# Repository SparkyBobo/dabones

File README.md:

# DaBones

DaBones is a Halloween animatronic rock show project combining mechanical characters, embedded electronics, lighting control, audio playback, and stage effects.

The goal is to create a repeatable live Halloween performance experience where animated characters perform as a band with synchronized movement, lighting, and effects.

## Project Status

Current release:

**DaBones v1.0 — Halloween 2026**

The focus of v1.0 is a complete, reliable show experience.

The goal is not to complete every possible feature. Future enhancements are intentionally deferred into later releases.

## System Overview

DaBones consists of several integrated systems:

* Animated characters
* Mechanical motion systems
* Embedded controllers
* Lighting and DMX control
* Audio and MIDI synchronization
* Stage infrastructure
* Special effects

## Engineering Approach

The project follows a release-based engineering model:

* Define the release before building
* Capture design decisions and tradeoffs
* Separate ideas from commitments
* Document why decisions are made
* Build platforms that support future expansion

## Repository Contents

```
docs/
    Release definitions
    Architecture documentation
    Inventory
    Decisions
    Field notes

hardware/
    Electronics designs
    Mechanical designs
    Related hardware files

firmware/
    Embedded software
```

## Relationship to Portfolio

DaBones is one project within a larger personal engineering portfolio.

The portfolio repository contains cross-project planning, engineering practices, and field notes.

## Current Goal

Deliver a complete Halloween 2026 show with a defined minimum viable feature set and a reliable operating experience.

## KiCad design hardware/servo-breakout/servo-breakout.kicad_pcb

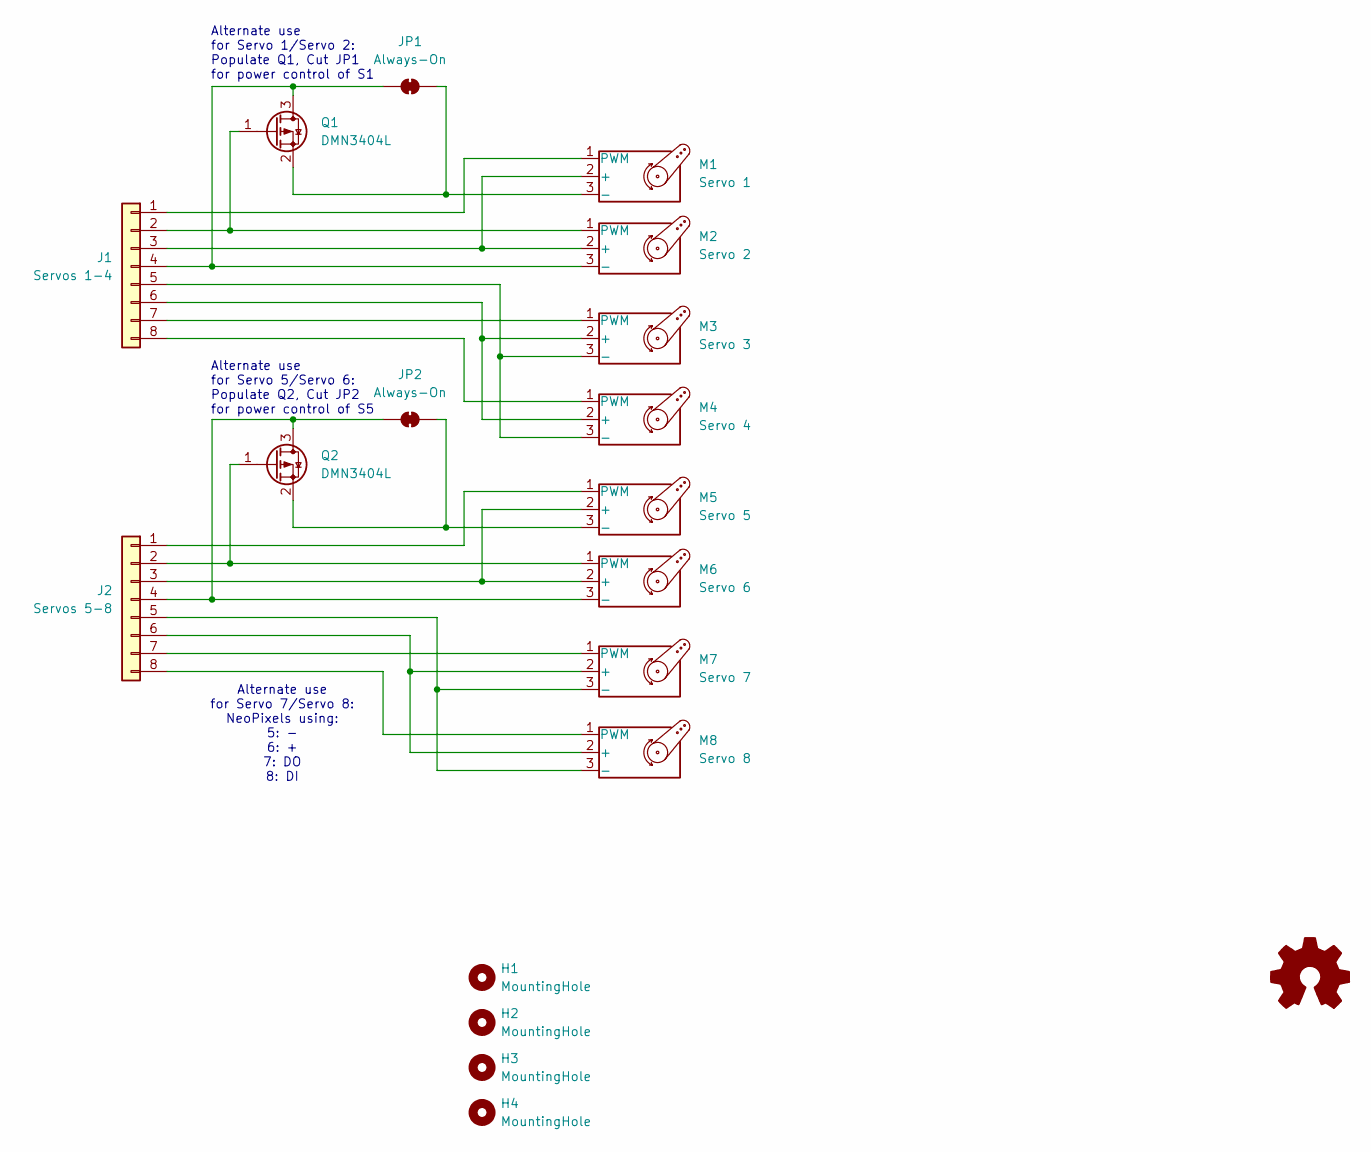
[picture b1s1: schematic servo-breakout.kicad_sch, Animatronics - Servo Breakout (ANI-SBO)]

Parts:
H1, H2, H3, H4: MountingHole; MountingHole_3.2mm_M3
J1: Servos 1-4; PhoenixContact_MCV_1,5_8-G-3.81_1x08_P3.81mm_Vertical
J2: Servos 5-8; PhoenixContact_MCV_1,5_8-G-3.81_1x08_P3.81mm_Vertical
JP1, JP2: Always-On; SolderJumper-2_P1.3mm_Bridged2Bar_RoundedPad1.0x1.5mm
M1: Servo 1; PinHeader_1x03_P2.54mm_Horizontal
M2: Servo 2; PinHeader_1x03_P2.54mm_Horizontal
M3: Servo 3; PinHeader_1x03_P2.54mm_Horizontal
M4: Servo 4; PinHeader_1x03_P2.54mm_Horizontal
M5: Servo 5; PinHeader_1x03_P2.54mm_Horizontal
M6: Servo 6; PinHeader_1x03_P2.54mm_Horizontal
M7: Servo 7; PinHeader_1x03_P2.54mm_Horizontal
M8: Servo 8; PinHeader_1x03_P2.54mm_Horizontal
Q1, Q2: DMN3404L; TSOT-23_HandSoldering

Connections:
unnamed: J1.1, M1.1 (PWM)
unnamed: J1.2, M2.1 (PWM), Q1.1 (G)
unnamed: J1.3, M1.2 (+), M2.2 (+)
unnamed: J1.4, JP1.2 (B), M2.3 (-), Q1.3 (D)
unnamed: J1.5, M3.3 (-), M4.3 (-)
unnamed: J1.6, M3.2 (+), M4.2 (+)
unnamed: J1.7, M3.1 (PWM)
unnamed: J1.8, M4.1 (PWM)
unnamed: J2.1, M5.1 (PWM)
unnamed: J2.2, M6.1 (PWM), Q2.1 (G)
unnamed: J2.3, M5.2 (+), M6.2 (+)
unnamed: J2.4, JP2.2 (B), M6.3 (-), Q2.3 (D)
unnamed: J2.5, M7.3 (-), M8.3 (-)
unnamed: J2.6, M7.2 (+), M8.2 (+)
unnamed: J2.7, M7.1 (PWM)
unnamed: J2.8, M8.1 (PWM)
unnamed: JP1.1 (A), M1.3 (-), Q1.2 (S)
unnamed: JP2.1 (A), M5.3 (-), Q2.2 (S)

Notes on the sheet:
Alternate use for Servo 7/Servo 8: NeoPixels using: 5: - 6: + 7: DO 8: DI
Alternate use for Servo 1/Servo 2: Populate Q1, Cut JP1 for power control of S1
Alternate use for Servo 5/Servo 6: Populate Q2, Cut JP2 for power control of S5

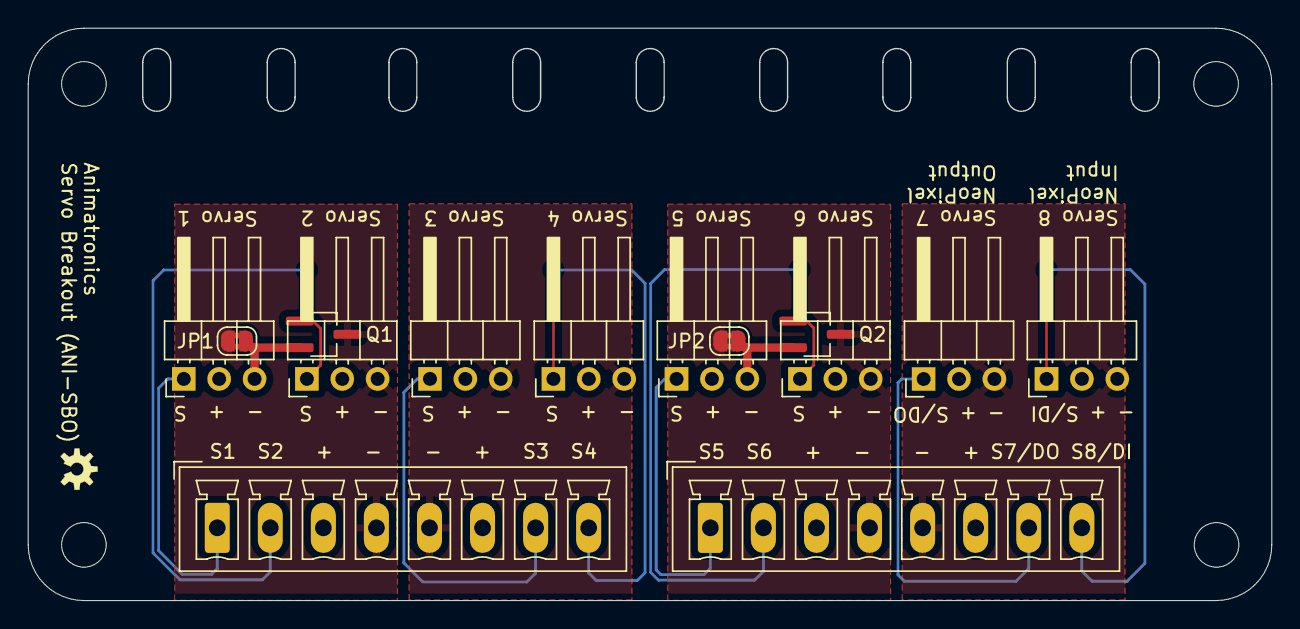
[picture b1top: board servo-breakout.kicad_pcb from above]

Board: 2 copper layers, 89.2 x 41.1 mm, 18 parts (0 on the bottom side), 18 nets.

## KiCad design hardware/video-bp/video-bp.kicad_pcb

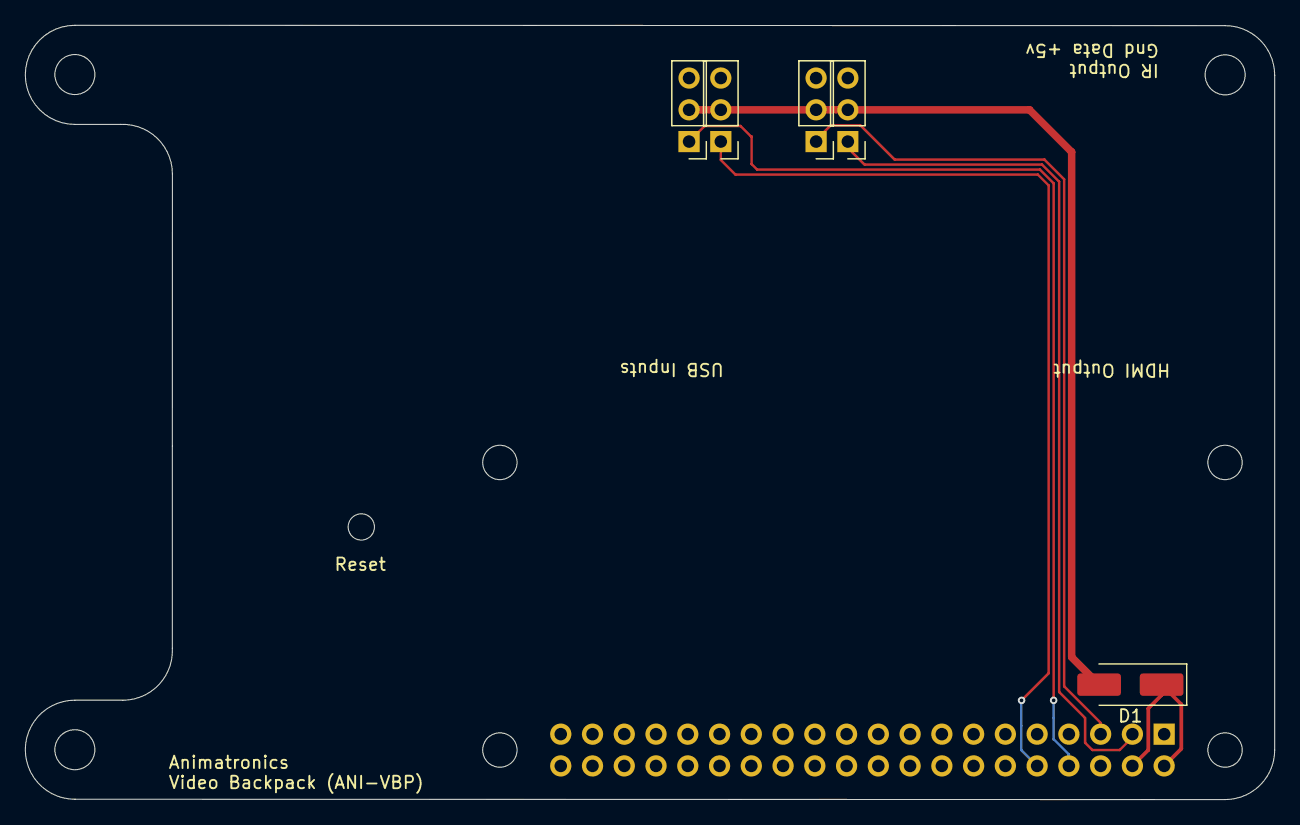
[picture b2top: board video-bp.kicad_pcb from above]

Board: 2 copper layers, 99.9 x 61.9 mm, 9 parts (1 on the bottom side), 7 nets.

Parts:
A1: Raspberry_Pi_2_3; Raspberry_Pi_Zero_Socketed_THT_FaceDown_MountingHoles
D1: MBRA340; D_SMA_Handsoldering
H1, H2, H3: MountingHole; MountingHole_3.2mm_M3
J1: GPIO9; PinHeader_1x03_P2.54mm_Vertical
J2: GPIO8; PinHeader_1x03_P2.54mm_Vertical
J3: GPIO5; PinHeader_1x03_P2.54mm_Vertical
J4: GPIO4; PinHeader_1x03_P2.54mm_Vertical

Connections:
+5VA: D1.2 (A), J1.2, J2.2, J3.2, J4.2
+5VP: A1.2 (5V), A1.4 (5V), D1.1 (K)
GND: A1.6 (GND), A1.9 (GND), A1.14 (GND), A1.20 (GND), A1.25 (GND), A1.30 (GND), A1.34 (GND), A1.39 (GND), J1.3, J2.3, J3.3, J4.3
unnamed: A1.8 (GPIO14/TXD), J1.1
unnamed: A1.10 (GPIO15/RXD), J2.1
unnamed: A1.5 (SCL/GPIO3), J3.1
unnamed: A1.3 (SDA/GPIO2), J4.1

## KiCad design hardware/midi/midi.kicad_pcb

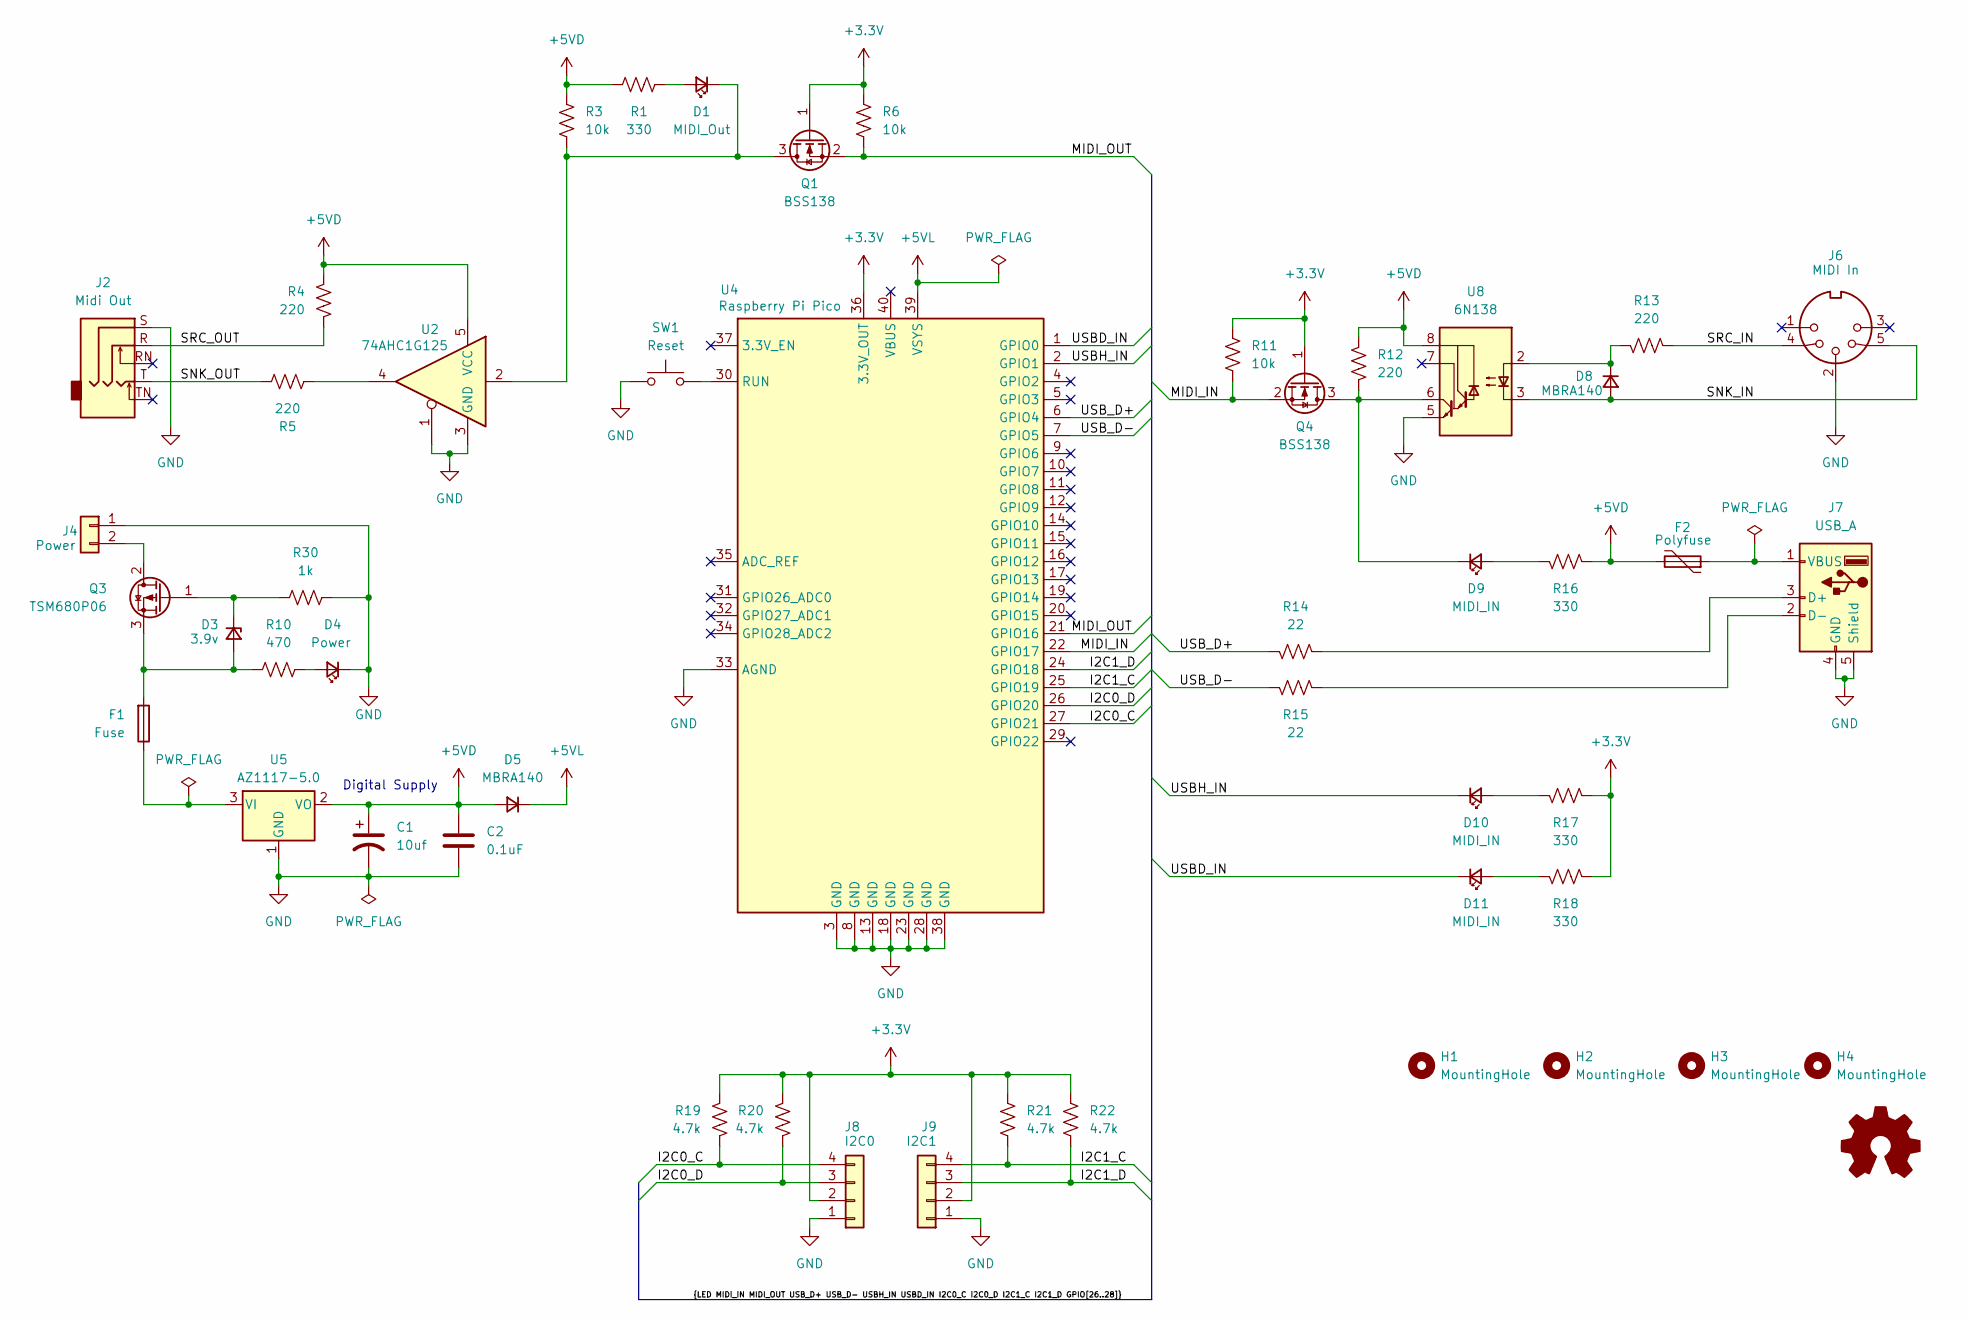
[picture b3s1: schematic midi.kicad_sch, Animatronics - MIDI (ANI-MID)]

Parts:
C1: 10uf; CP_Radial_D5.0mm_P2.00mm
C2: 0.1uF; C_Rect_L4.0mm_W2.5mm_P2.50mm
D1: MIDI_Out; LED_1206_3216Metric_Pad1.42x1.75mm_HandSolder
D3: 3.9v; D_SOD-123
D4: Power; LED_1206_3216Metric_Pad1.42x1.75mm_HandSolder
D5, D8: MBRA140; D_SMA_Handsoldering
D9, D10, D11: MIDI_IN; LED_1206_3216Metric_Pad1.42x1.75mm_HandSolder
F1: Fuse; atc_fuse_vertical
F2: Polyfuse; Fuse_1206_3216Metric_Pad1.42x1.75mm_HandSolder
H1, H2, H3, H4: MountingHole; MountingHole_3.2mm_M3
J2: Midi Out; Jack_3.5mm_Adafruit_1699_Horizontal
J4: Power; PhoenixContact_MC_1,5_2-G-3.81_1x02_P3.81mm_Horizontal
J6: MIDI In; MIDI_DIN_5
J7: USB_A; USB_A_Molex_67643_Horizontal
J8: I2C0; JST_SH_BM04B-SRSS-TB_1x04-1MP_P1.00mm_Vertical
J9: I2C1; JST_SH_BM04B-SRSS-TB_1x04-1MP_P1.00mm_Vertical
Q1, Q4: BSS138; SOT-23
Q3: TSM680P06; TO-252-2
R1, R16, R17, R18: 330; R_1206_3216Metric_Pad1.30x1.75mm_HandSolder
R3, R6, R11: 10k; R_1206_3216Metric_Pad1.30x1.75mm_HandSolder
R4, R5, R12, R13: 220; R_1206_3216Metric_Pad1.30x1.75mm_HandSolder
R10: 470; R_1206_3216Metric_Pad1.30x1.75mm_HandSolder
R14, R15: 22; R_1206_3216Metric_Pad1.30x1.75mm_HandSolder
R19, R20, R21, R22: 4.7k; R_1206_3216Metric_Pad1.30x1.75mm_HandSolder
R30: 1k; R_1206_3216Metric_Pad1.30x1.75mm_HandSolder
SW1: Reset; SW_PUSH_6mm
U2: 74AHC1G125; SOT-23-5_HandSoldering
U4: Raspberry Pi Pico; DIP-40_W15.24mm
U5: AZ1117-5.0; SOT-223-3_TabPin2
U8: 6N138; SMDIP-8_W9.53mm

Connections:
+3.3V: J8.2, J9.2, Q1.1 (G), Q4.1 (G), R6.2, R11.2, R17.2, R18.2, R19.2, R20.2, R21.2, R22.2, U4.36 (3.3V_OUT)
+5VD: C1.1, C2.1, D5.2 (A), F2.2, R1.2, R3.1, R4.2, R12.1, R16.2, U2.5 (VCC), U5.2 (VO), U8.8 (VCC)
+5VL: D5.1 (K), U4.39 (VSYS)
/I2C0_C: J8.4, R19.1, U4.27 (GPIO21)
/I2C0_D: J8.3, R20.1, U4.26 (GPIO20)
/I2C1_C: J9.4, R21.1, U4.25 (GPIO19)
/I2C1_D: J9.3, R22.1, U4.24 (GPIO18)
/MIDI_IN: Q4.2 (S), R11.1, U4.22 (GPIO17)
/MIDI_OUT: Q1.2 (S), R6.1, U4.21 (GPIO16)
/SNK_IN: D8.2 (A), J6.5, U8.3 (C2)
/SNK_OUT: J2.T, R5.2
/SRC_IN: J6.4, R13.1
/SRC_OUT: J2.R, R4.1
/USBD_IN: D11.1 (K), U4.1 (GPIO0)
/USBH_IN: D10.1 (K), U4.2 (GPIO1)
/USB_D+: R14.2, U4.6 (GPIO4)
/USB_D-: R15.1, U4.7 (GPIO5)
GND: C1.2, C2.2, D4.1 (K), J2.S, J4.1, J6.2, J7.4 (GND), J7.5 (Shield), J8.1, J9.1, R30.2, SW1.1, U2.1, U2.3 (GND), U4.3 (GND), U4.8 (GND), U4.13 (GND), U4.18 (GND), U4.23 (GND), U4.28 (GND), U4.33 (AGND), U4.38 (GND), U5.1 (GND), U8.5 (GND)
unnamed: D1.2 (A), R1.1
unnamed: D1.1 (K), Q1.3 (D), R3.2, U2.2
unnamed: D3.2 (A), F1.2, Q3.3 (S), R10.1
unnamed: D3.1 (K), Q3.1 (G), R30.1
unnamed: D4.2 (A), R10.2
unnamed: D8.1 (K), R13.2, U8.2 (C1)
unnamed: D9.2 (A), R16.1
unnamed: D9.1 (K), Q4.3 (D), R12.2, U8.6 (VO2)
unnamed: D10.2 (A), R17.1
unnamed: D11.2 (A), R18.1
unnamed: J4.2, Q3.2 (D)
unnamed: J7.3 (D+), R14.1
unnamed: J7.2 (D-), R15.2
unnamed: F2.1, J7.1 (VBUS)
unnamed: R5.1, U2.4
unnamed: SW1.2, U4.30 (RUN)
unnamed: F1.1, U5.3 (VI)

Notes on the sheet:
Digital Supply

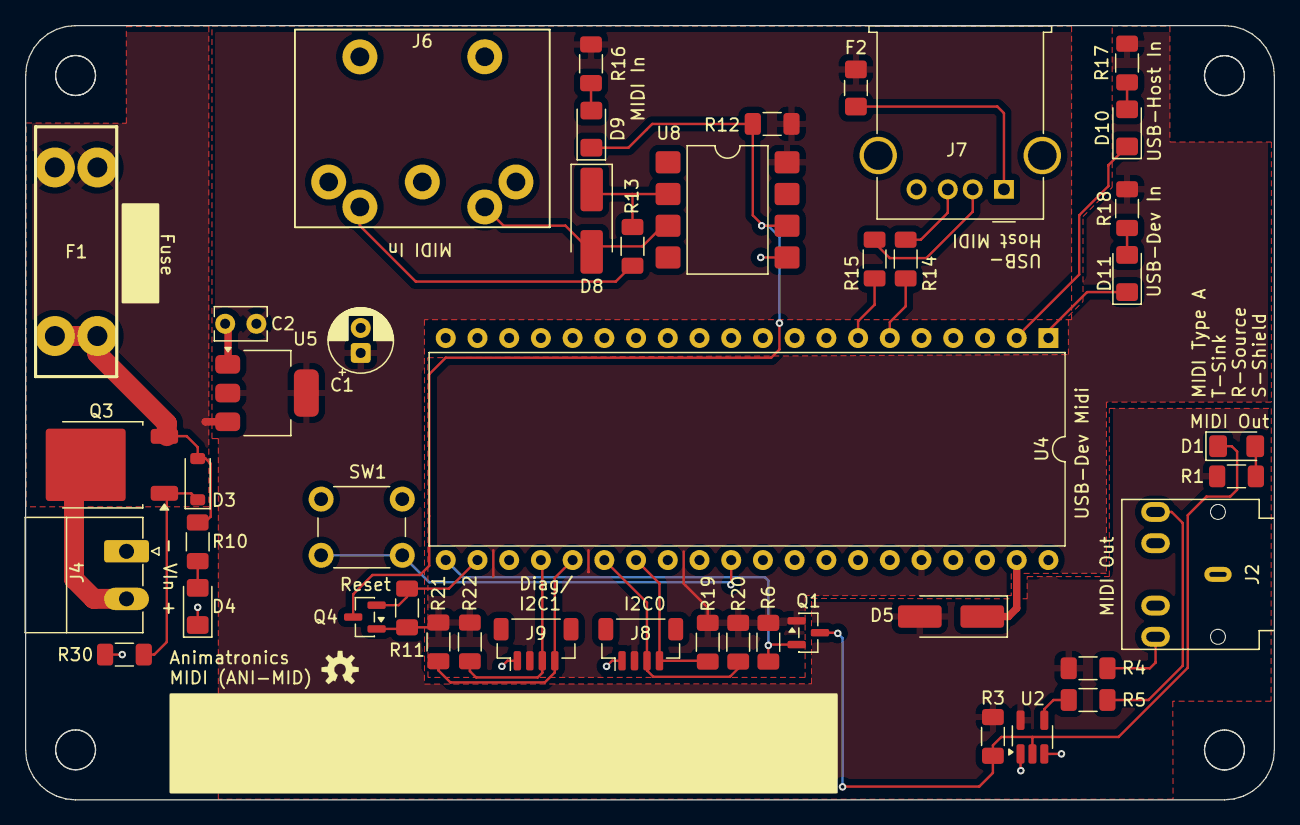
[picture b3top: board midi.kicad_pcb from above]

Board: 2 copper layers, 100.0 x 62.0 mm, 49 parts (0 on the bottom side), 35 nets.

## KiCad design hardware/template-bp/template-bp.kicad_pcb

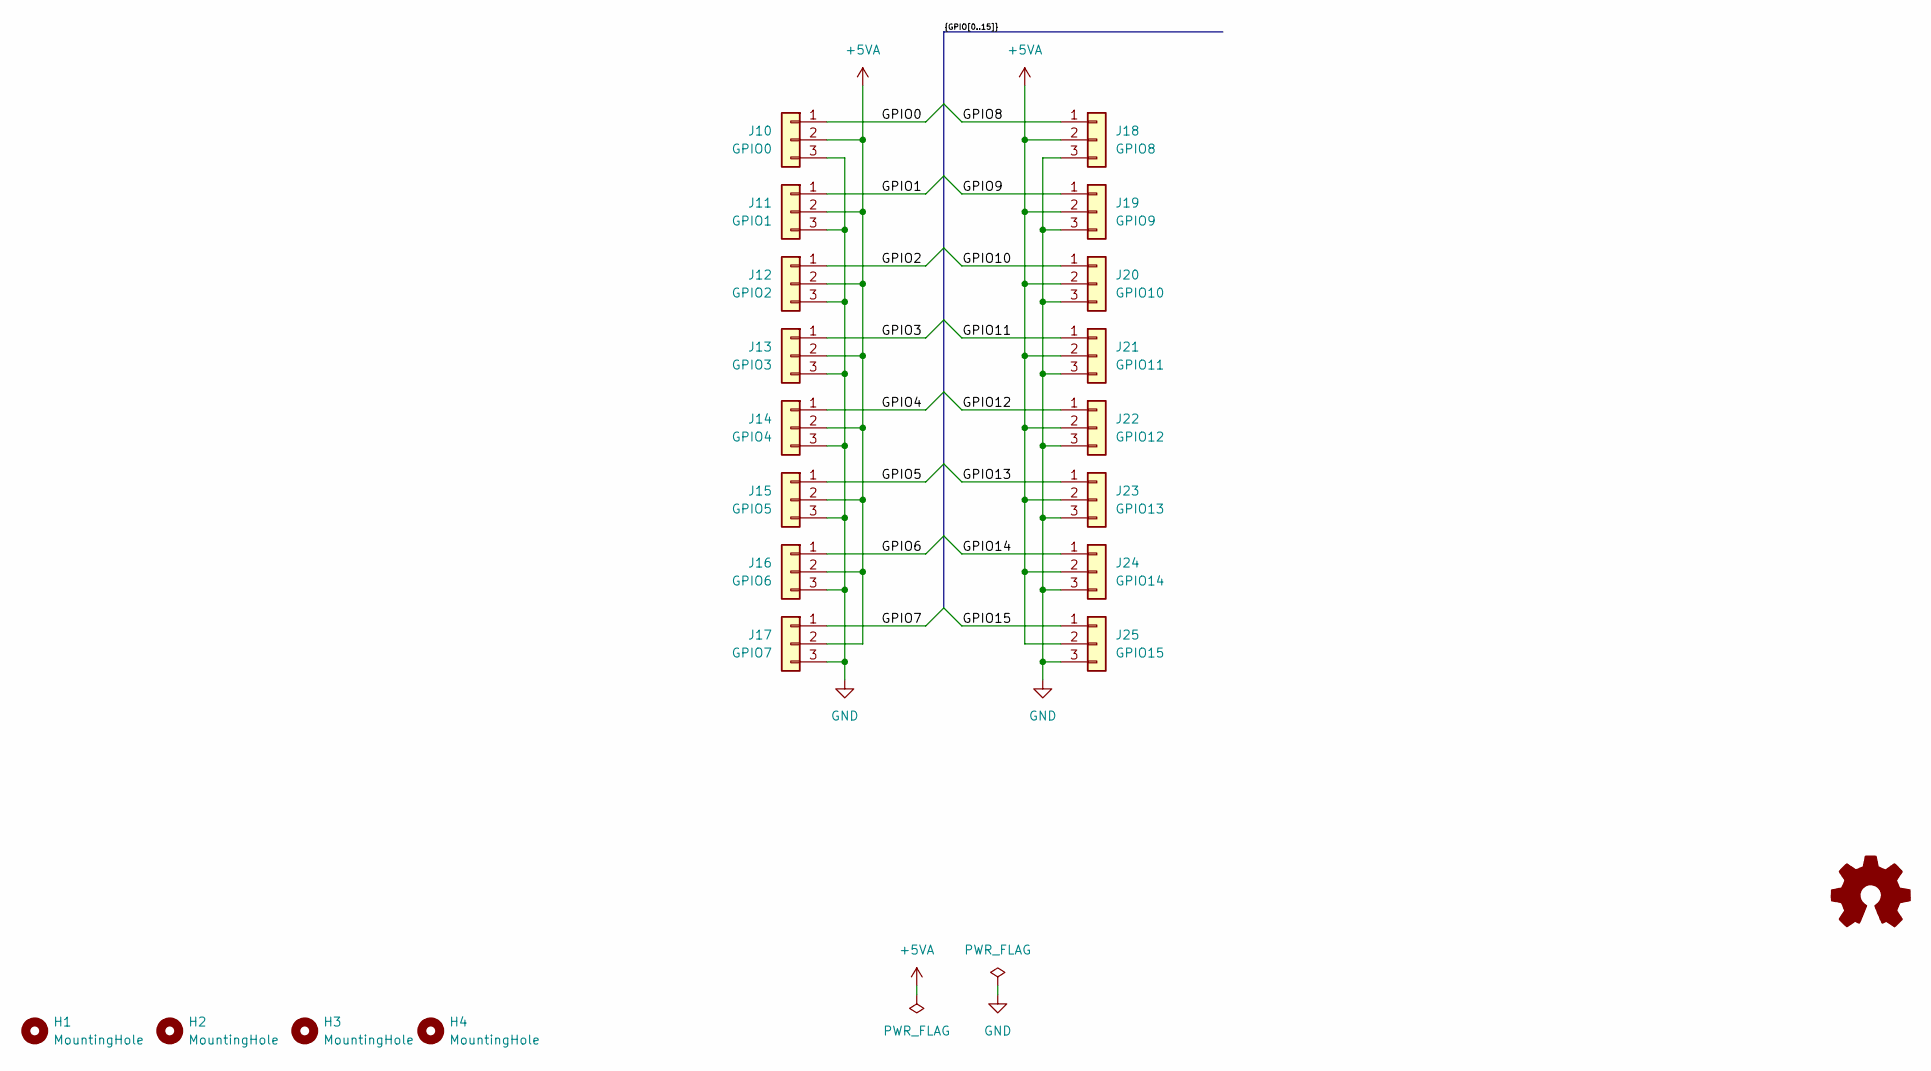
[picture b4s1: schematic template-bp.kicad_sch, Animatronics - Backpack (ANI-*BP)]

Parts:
H1, H2, H3, H4: MountingHole; MountingHole_3.2mm_M3
J10: GPIO0; PinHeader_1x03_P2.54mm_Vertical
J11: GPIO1; PinHeader_1x03_P2.54mm_Vertical
J12: GPIO2; PinHeader_1x03_P2.54mm_Vertical
J13: GPIO3; PinHeader_1x03_P2.54mm_Vertical
J14: GPIO4; PinHeader_1x03_P2.54mm_Vertical
J15: GPIO5; PinHeader_1x03_P2.54mm_Vertical
J16: GPIO6; PinHeader_1x03_P2.54mm_Vertical
J17: GPIO7; PinHeader_1x03_P2.54mm_Vertical
J18: GPIO8; PinHeader_1x03_P2.54mm_Vertical
J19: GPIO9; PinHeader_1x03_P2.54mm_Vertical
J20: GPIO10; PinHeader_1x03_P2.54mm_Vertical
J21: GPIO11; PinHeader_1x03_P2.54mm_Vertical
J22: GPIO12; PinHeader_1x03_P2.54mm_Vertical
J23: GPIO13; PinHeader_1x03_P2.54mm_Vertical
J24: GPIO14; PinHeader_1x03_P2.54mm_Vertical
J25: GPIO15; PinHeader_1x03_P2.54mm_Vertical

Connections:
+5VA: J10.2, J11.2, J12.2, J13.2, J14.2, J15.2, J16.2, J17.2, J18.2, J19.2, J20.2, J21.2, J22.2, J23.2, J24.2, J25.2
/GPIO0: J10.1
/GPIO1: J11.1
/GPIO2: J12.1
/GPIO3: J13.1
/GPIO4: J14.1
/GPIO5: J15.1
/GPIO6: J16.1
/GPIO7: J17.1
/GPIO8: J18.1
/GPIO9: J19.1
/GPIO10: J20.1
/GPIO11: J21.1
/GPIO12: J22.1
/GPIO13: J23.1
/GPIO14: J24.1
/GPIO15: J25.1
GND: J10.3, J11.3, J12.3, J13.3, J14.3, J15.3, J16.3, J17.3, J18.3, J19.3, J20.3, J21.3, J22.3, J23.3, J24.3, J25.3

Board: 2 copper layers, 20 parts (0 on the bottom side), 2 nets, no tracks yet.

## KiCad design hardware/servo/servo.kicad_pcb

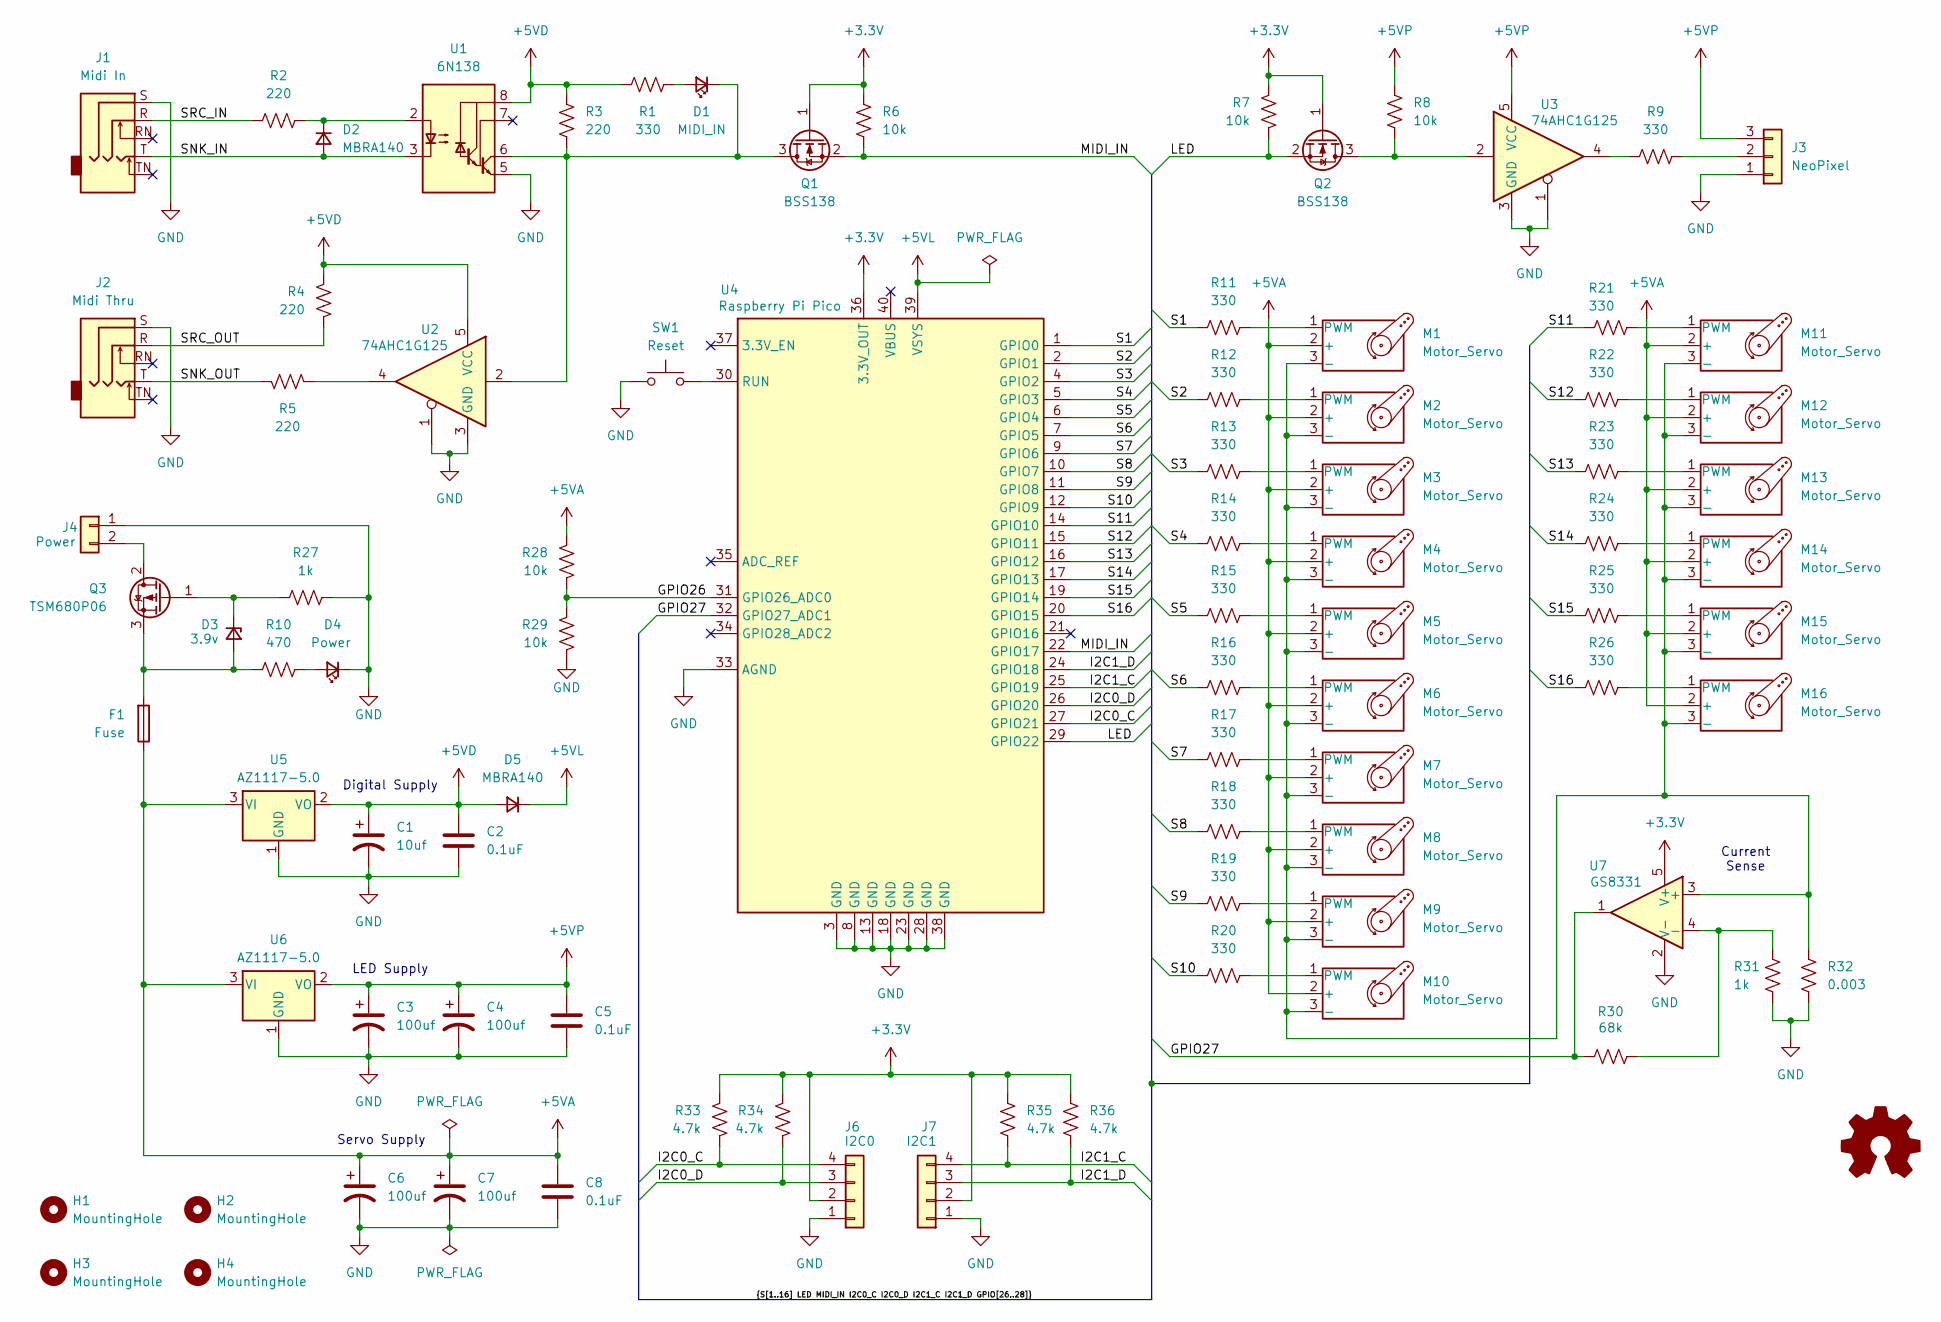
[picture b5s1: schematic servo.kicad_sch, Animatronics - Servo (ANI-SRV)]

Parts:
C1: 10uf; CP_Radial_D5.0mm_P2.00mm
C2, C5, C8: 0.1uF; C_Rect_L4.0mm_W2.5mm_P2.50mm
C3, C4, C6, C7: 100uf; CP_Radial_D5.0mm_P2.00mm
D1: MIDI_IN; LED_1206_3216Metric_Pad1.42x1.75mm_HandSolder
D2, D5: MBRA140; D_SMA_Handsoldering
D3: 3.9v; D_SOD-123
D4: Power; LED_1206_3216Metric_Pad1.42x1.75mm_HandSolder
F1: Fuse; atc_fuse_vertical
H1, H2, H3, H4: MountingHole; MountingHole_3.2mm_M3
J1: Midi In; Jack_3.5mm_Adafruit_1699_Horizontal
J2: Midi Thru; Jack_3.5mm_Adafruit_1699_Horizontal
J3: NeoPixel; PhoenixContact_MC_1,5_3-G-3.81_1x03_P3.81mm_Horizontal
J4: Power; PhoenixContact_MC_1,5_2-G-3.81_1x02_P3.81mm_Horizontal
J6: I2C0; JST_SH_BM04B-SRSS-TB_1x04-1MP_P1.00mm_Vertical
J7: I2C1; JST_SH_BM04B-SRSS-TB_1x04-1MP_P1.00mm_Vertical
M1, M2, M3, M4, M5, M6, M7, M8, M9, M10, M11, M12, M13, M14, M15, M16: Motor_Servo; PinHeader_1x03_P2.54mm_Vertical
Q1, Q2: BSS138; SOT-23
Q3: TSM680P06; TO-252-2
R1, R9, R11, R12, R13, R14, R15, R16, R17, R18, R19, R20, R21, R22, R23, R24, R25, R26: 330; R_1206_3216Metric_Pad1.30x1.75mm_HandSolder
R2, R3, R4, R5: 220; R_1206_3216Metric_Pad1.30x1.75mm_HandSolder
R6, R7, R8, R28, R29: 10k; R_1206_3216Metric_Pad1.30x1.75mm_HandSolder
R10: 470; R_1206_3216Metric_Pad1.30x1.75mm_HandSolder
R27, R31: 1k; R_1206_3216Metric_Pad1.30x1.75mm_HandSolder
R30: 68k; R_1206_3216Metric_Pad1.30x1.75mm_HandSolder
R32: 0.003; R_1206_3216Metric_Pad1.30x1.75mm_HandSolder
R33, R34, R35, R36: 4.7k; R_1206_3216Metric_Pad1.30x1.75mm_HandSolder
SW1: Reset; SW_PUSH_6mm
U1: 6N138; SMDIP-8_W9.53mm
U2, U3: 74AHC1G125; SOT-23-5_HandSoldering
U4: Raspberry Pi Pico; RP_Pico_DIP
U5, U6: AZ1117-5.0; SOT-223-3_TabPin2
U7: GS8331; TSOT-23-5

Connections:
+3.3V: J6.2, J7.2, Q1.1 (G), Q2.1 (G), R6.2, R7.2, R33.2, R34.2, R35.2, R36.2, U4.36 (3.3V_OUT), U7.5 (V+)
+5VA: C6.1, C7.1, C8.1, F1.1, M1.2 (+), M2.2 (+), M3.2 (+), M4.2 (+), M5.2 (+), M6.2 (+), M7.2 (+), M8.2 (+), M9.2 (+), M10.2 (+), M11.2 (+), M12.2 (+), M13.2 (+), M14.2 (+), M15.2 (+), M16.2 (+), R28.2, U5.3 (VI), U6.3 (VI)
+5VD: C1.1, C2.1, D5.2 (A), R1.2, R3.1, R4.2, U1.8 (VCC), U2.5 (VCC), U5.2 (VO)
+5VL: D5.1 (K), U4.39 (VSYS)
+5VP: C3.1, C4.1, C5.1, J3.3, R8.2, U3.5 (VCC), U6.2 (VO)
/GPIO26: R28.1, R29.2, U4.31 (GPIO26_ADC0)
/GPIO27: R30.1, U4.32 (GPIO27_ADC1), U7.1
/I2C0_C: J6.4, R33.1, U4.27 (GPIO21)
/I2C0_D: J6.3, R34.1, U4.26 (GPIO20)
/I2C1_C: J7.4, R35.1, U4.25 (GPIO19)
/I2C1_D: J7.3, R36.1, U4.24 (GPIO18)
/LED: Q2.2 (S), R7.1, U4.29 (GPIO22)
/MIDI_IN: Q1.2 (S), R6.1, U4.22 (GPIO17)
/S1: R11.1, U4.1 (GPIO0)
/S2: R12.1, U4.2 (GPIO1)
/S3: R13.1, U4.4 (GPIO2)
/S4: R14.1, U4.5 (GPIO3)
/S5: R15.1, U4.6 (GPIO4)
/S6: R16.1, U4.7 (GPIO5)
/S7: R17.1, U4.9 (GPIO6)
/S8: R18.1, U4.10 (GPIO7)
/S9: R19.1, U4.11 (GPIO8)
/S10: R20.1, U4.12 (GPIO9)
/S11: R21.1, U4.14 (GPIO10)
/S12: R22.1, U4.15 (GPIO11)
/S13: R23.1, U4.16 (GPIO12)
/S14: R24.1, U4.17 (GPIO13)
/S15: R25.1, U4.19 (GPIO14)
/S16: R26.1, U4.20 (GPIO15)
/SNK_IN: D2.2 (A), J1.T, U1.3 (C2)
/SNK_OUT: J2.T, R5.1
/SRC_IN: J1.R, R2.1
/SRC_OUT: J2.R, R4.1
GND: C1.2, C2.2, C3.2, C4.2, C5.2, C6.2, C7.2, C8.2, D4.1 (K), J1.S, J2.S, J3.1, J4.1, J6.1, J7.1, R27.2, R29.1, R31.1, R32.1, SW1.1, U1.5 (GND), U2.1, U2.3 (GND), U3.1, U3.3 (GND), U4.3 (GND), U4.8 (GND), U4.13 (GND), U4.18 (GND), U4.23 (GND), U4.28 (GND), U4.33 (AGND), U4.38 (GND), U5.1 (GND), U6.1 (GND), U7.2 (V-)
unnamed: D1.2 (A), R1.1
unnamed: D1.1 (K), Q1.3 (D), R3.2, U1.6 (VO2), U2.2
unnamed: D2.1 (K), R2.2, U1.2 (C1)
unnamed: D3.2 (A), F1.2, Q3.3 (S), R10.1
unnamed: D3.1 (K), Q3.1 (G), R27.1
unnamed: D4.2 (A), R10.2
unnamed: J3.2, R9.2
unnamed: J4.2, Q3.2 (D)
unnamed: M1.3 (-), M2.3 (-), M3.3 (-), M4.3 (-), M5.3 (-), M6.3 (-), M7.3 (-), M8.3 (-), M9.3 (-), M10.3 (-), M11.3 (-), M12.3 (-), M13.3 (-), M14.3 (-), M15.3 (-), M16.3 (-), R32.2, U7.3 (+)
unnamed: M1.1 (PWM), R11.2
unnamed: M2.1 (PWM), R12.2
unnamed: M3.1 (PWM), R13.2
unnamed: M4.1 (PWM), R14.2
unnamed: M5.1 (PWM), R15.2
unnamed: M6.1 (PWM), R16.2
unnamed: M7.1 (PWM), R17.2
unnamed: M8.1 (PWM), R18.2
unnamed: M9.1 (PWM), R19.2
unnamed: M10.1 (PWM), R20.2
unnamed: M11.1 (PWM), R21.2
unnamed: M12.1 (PWM), R22.2
unnamed: M13.1 (PWM), R23.2
unnamed: M14.1 (PWM), R24.2
unnamed: M15.1 (PWM), R25.2
unnamed: M16.1 (PWM), R26.2
unnamed: Q2.3 (D), R8.1, U3.2
unnamed: R5.2, U2.4
unnamed: R9.1, U3.4
unnamed: SW1.2, U4.30 (RUN)
unnamed: R30.2, R31.2, U7.4 (-)

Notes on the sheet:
Current Sense
LED Supply
Digital Supply
Servo Supply

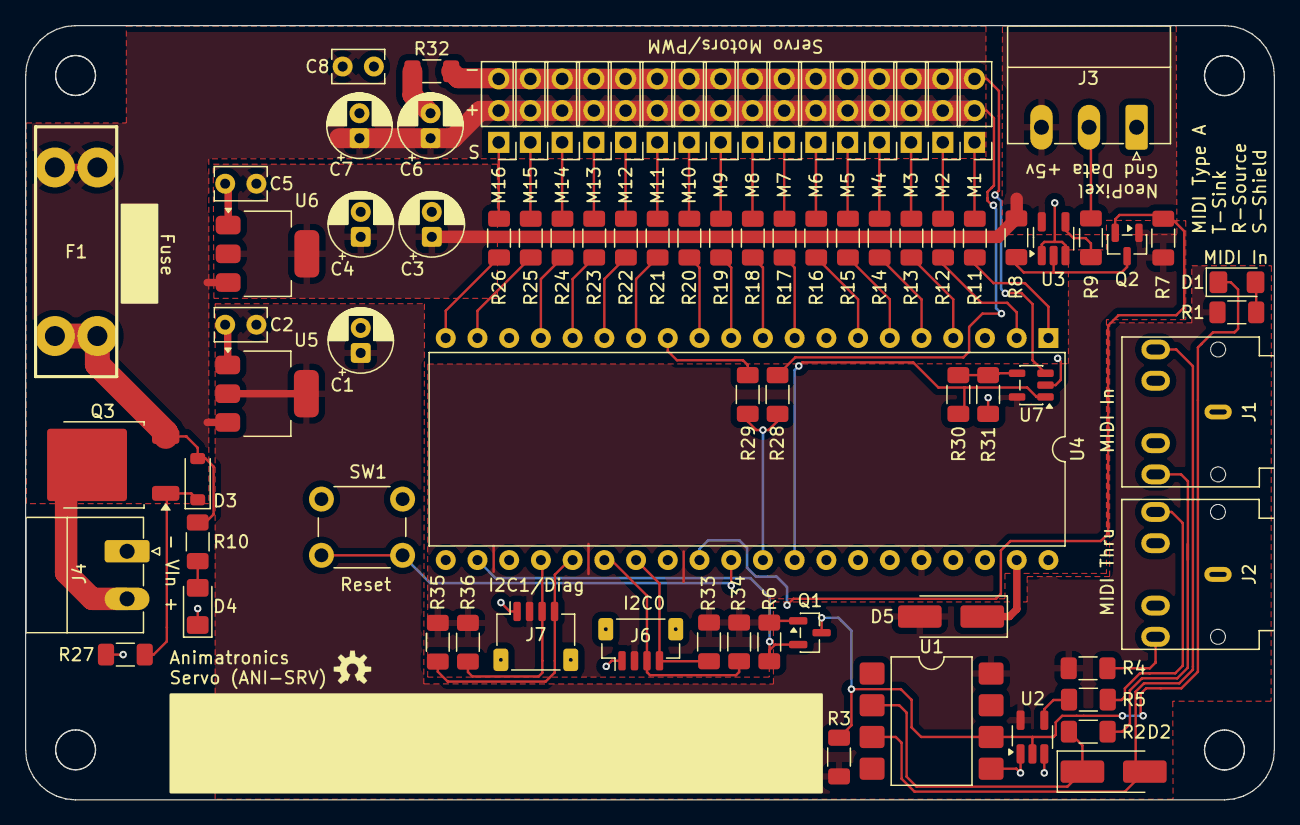
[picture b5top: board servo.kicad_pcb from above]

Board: 2 copper layers, 100.0 x 62.0 mm, 87 parts (0 on the bottom side), 64 nets.

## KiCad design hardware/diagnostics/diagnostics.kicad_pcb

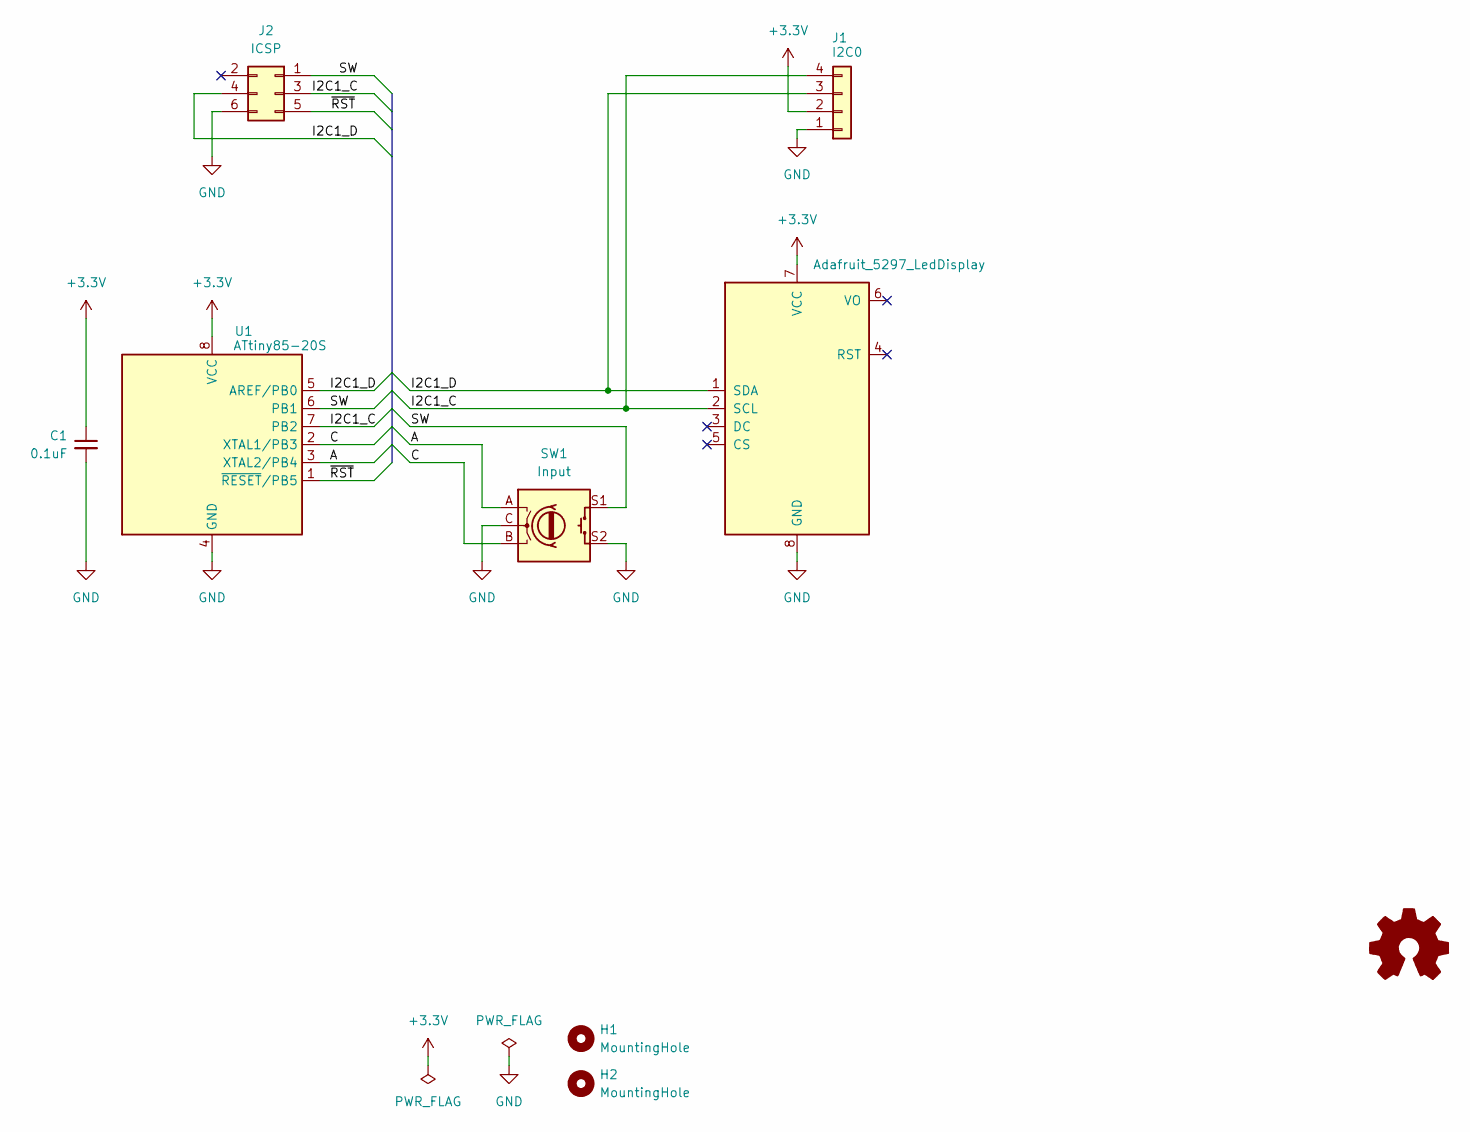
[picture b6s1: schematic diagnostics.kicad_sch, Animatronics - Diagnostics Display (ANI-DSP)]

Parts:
C1: 0.1uF; C_1206_3216Metric_Pad1.33x1.80mm_HandSolder
DS1: Adafruit_5297_LedDisplay; Adafruit_5297
H1, H2: MountingHole; MountingHole_3.2mm_M3
J1: I2C0; JST_SH_SM04B-SRSS-TB_1x04-1MP_P1.00mm_Horizontal
J2: ICSP; PinHeader_2x03_P2.54mm_Vertical
SW1: Input; RotaryEncoder_Bourns_Vertical_PEC12R-3x17F-Sxxxx
U1: ATtiny85-20S; SOIC-8_3.9x4.9mm_P1.27mm

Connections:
+3.3V: C1.1, DS1.7 (VCC), J1.2, U1.8 (VCC); also elsewhere on the board
/A: SW1.A, U1.3 (XTAL2/PB4)
/B: SW1.B, U1.2 (XTAL1/PB3)
/I2C1_C: DS1.2 (SCL), J1.4, J2.3, U1.7 (PB2)
/I2C1_D: DS1.1 (SDA), J1.3, J2.4, U1.5 (AREF/PB0)
/SW: J2.1, SW1.S1, U1.6 (PB1)
/~RST: J2.5, U1.1 (~RESET/PB5)
GND: C1.2, DS1.8 (GND), J1.1, J2.6, SW1.C, SW1.S2, U1.4 (GND)
unnamed 8: J2.2; also elsewhere on the board

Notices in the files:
hardware/diagnostics/diagnostics.kicad_pcb:
https://creativecommons.org/licenses/by-sa/4.0
Released under the Creative Commons Attribution Share-Alike 4.0 License
